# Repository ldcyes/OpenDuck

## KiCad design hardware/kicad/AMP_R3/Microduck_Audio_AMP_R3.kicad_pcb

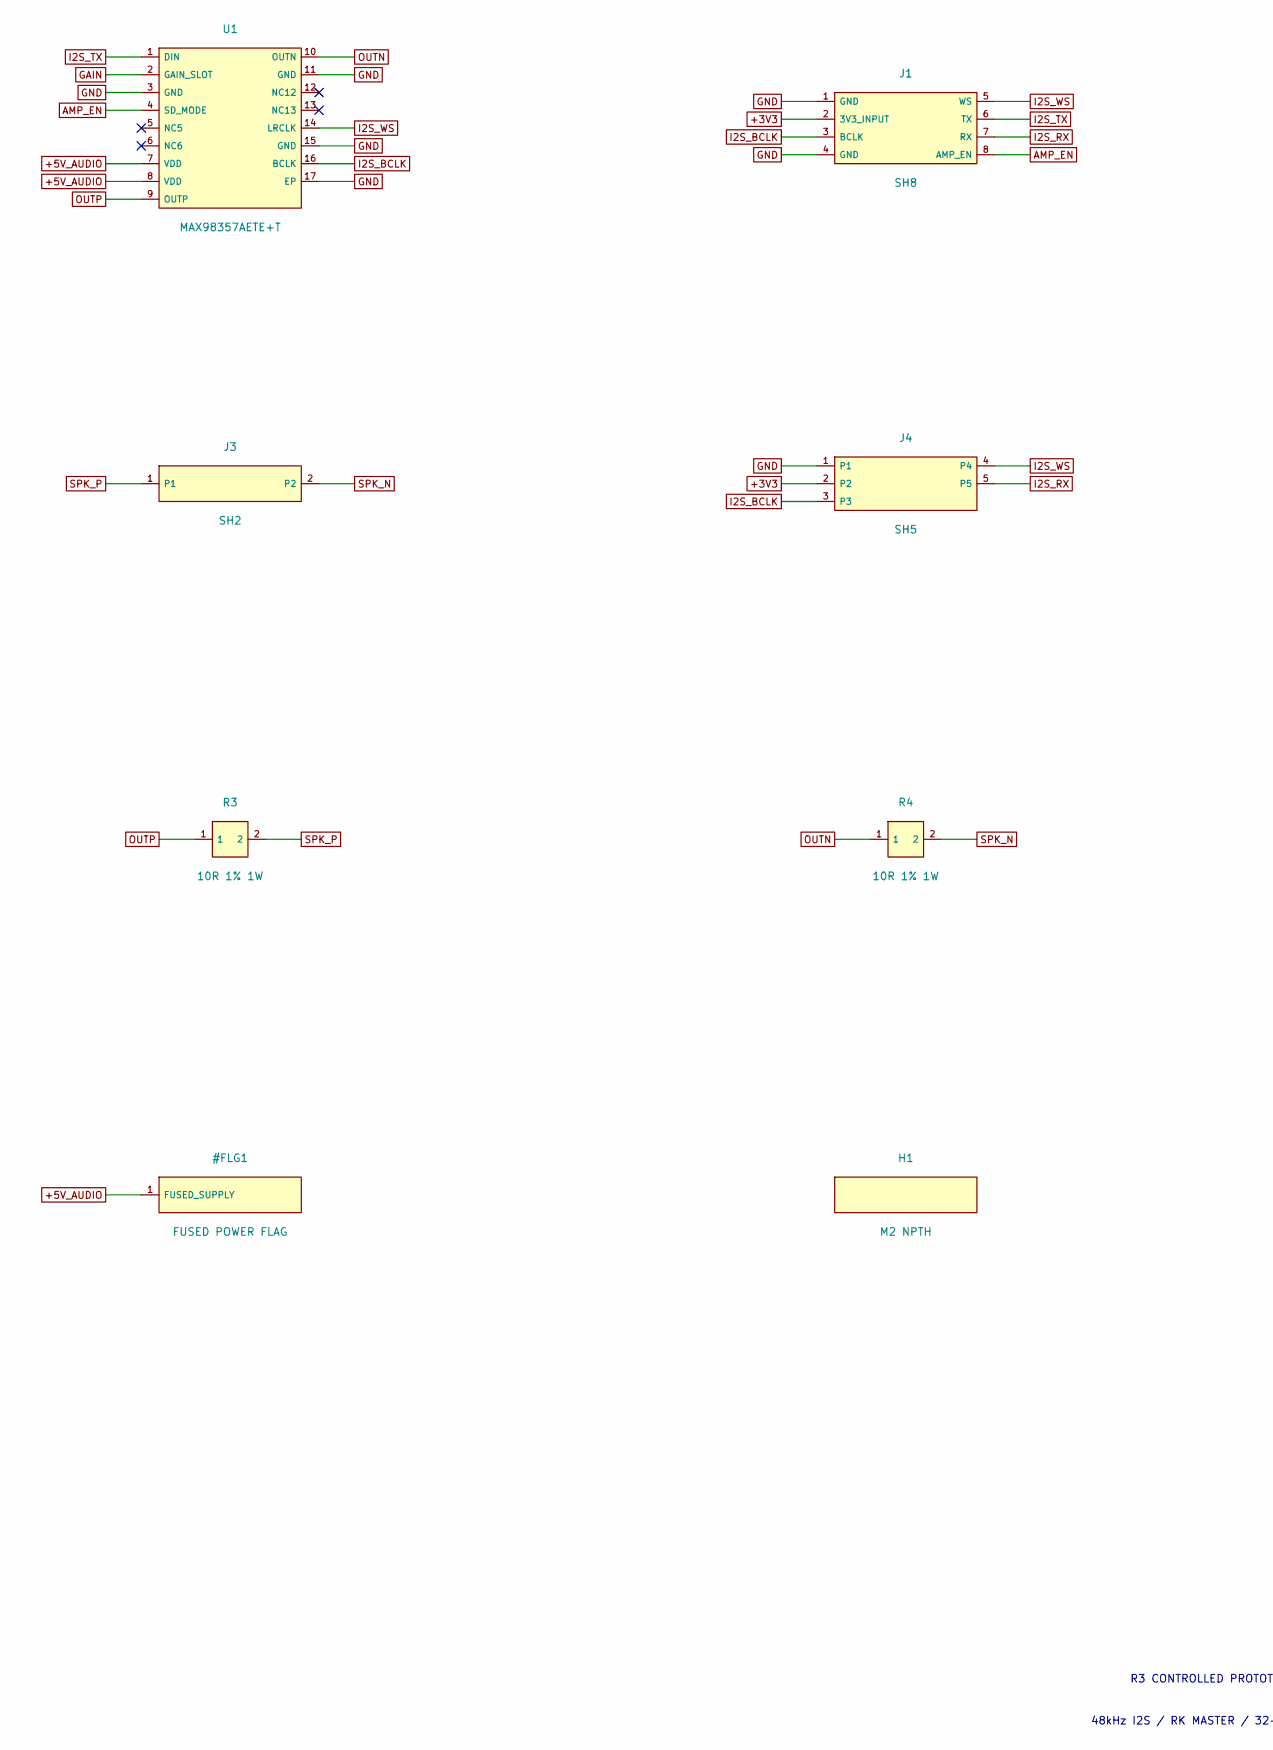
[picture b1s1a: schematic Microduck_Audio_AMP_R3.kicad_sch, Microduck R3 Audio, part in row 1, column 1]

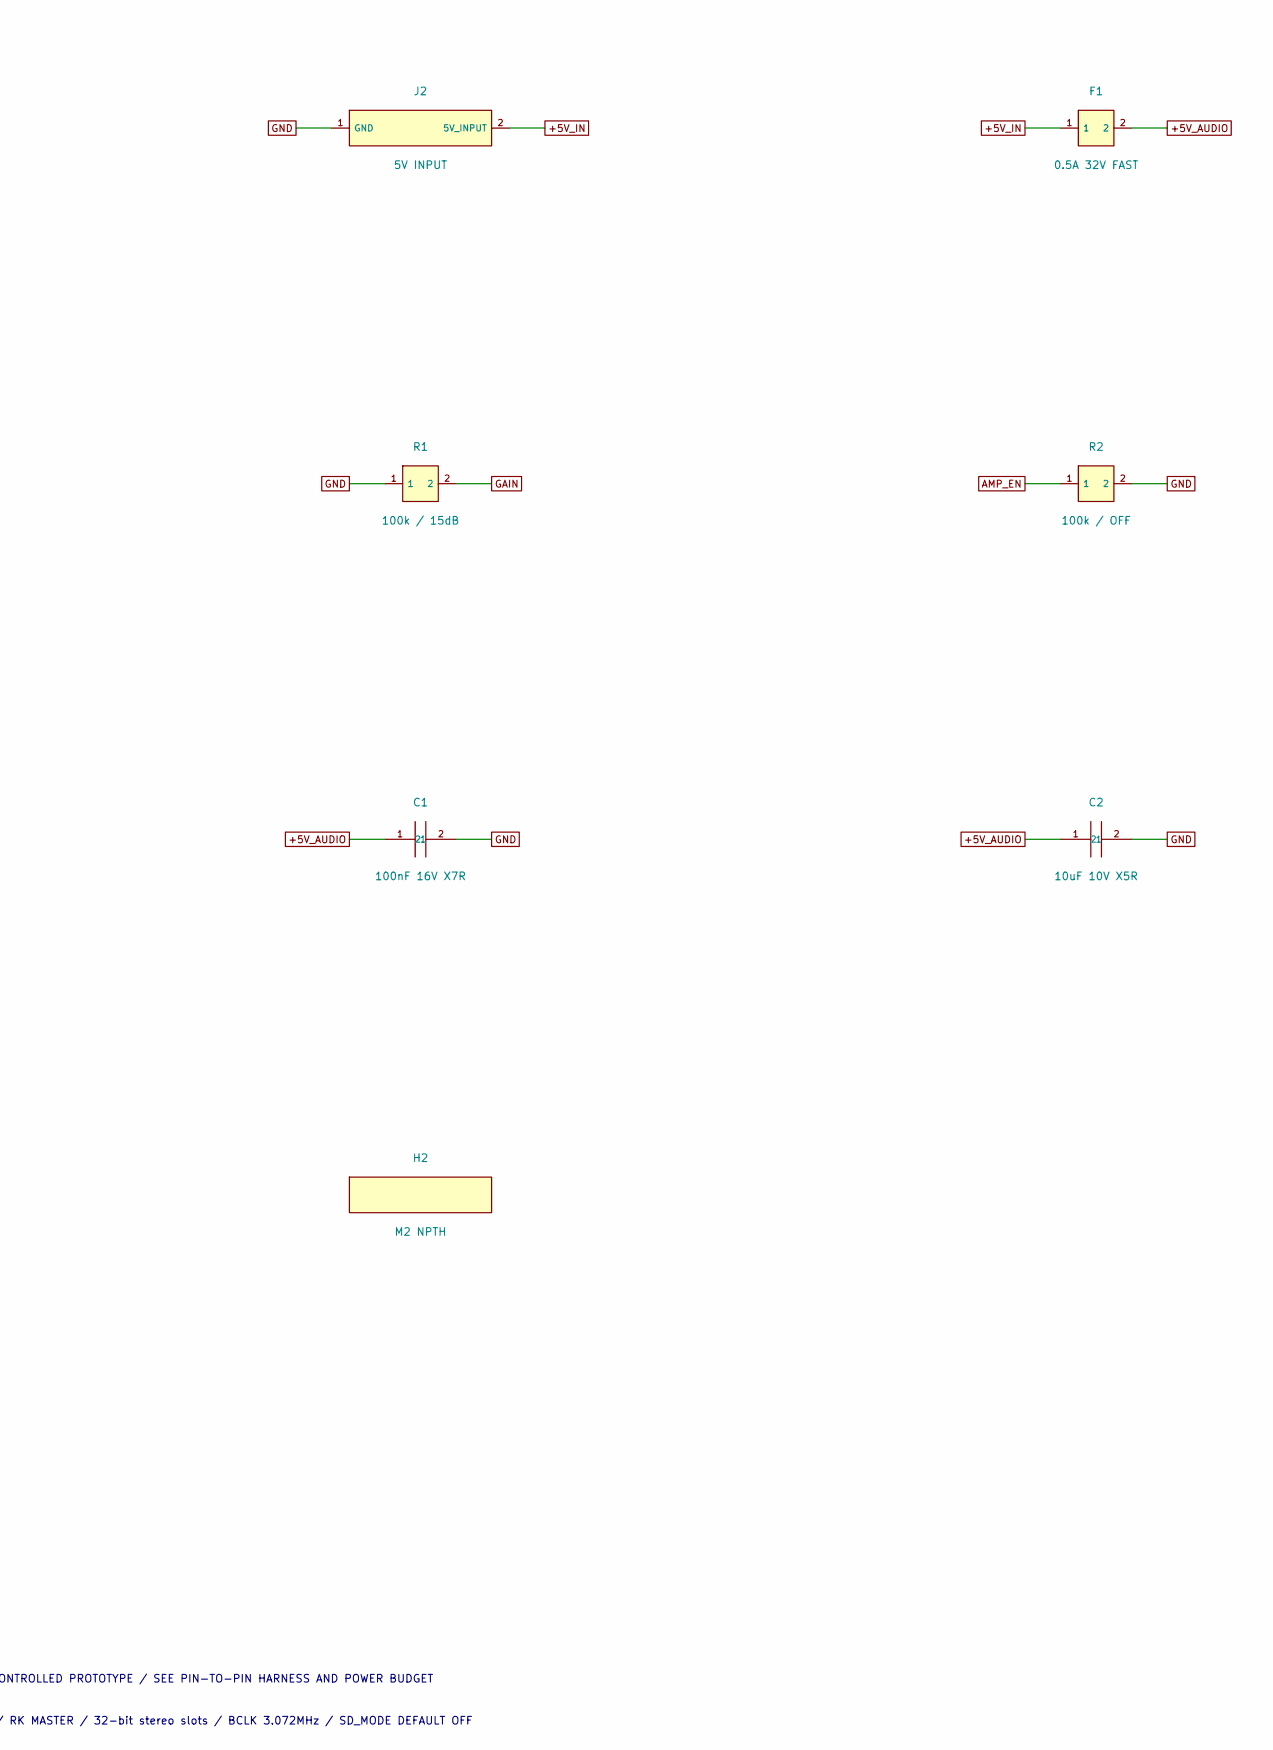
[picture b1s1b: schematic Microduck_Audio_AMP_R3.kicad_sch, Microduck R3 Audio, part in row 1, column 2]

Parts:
C1: 100nF 16V X7R; C_0603_1608Metric; MPN GRM188R71C104KA01D
C2: 10uF 10V X5R; C_0603_1608Metric; MPN GRM188R61A106KE69D
F1: 0.5A 32V FAST; Fuse_0603_1608Metric; MPN 0467.500NR
H1, H2: M2 NPTH; MountingHole_2.2mm_M2; MPN NO PART
J1: SH8; JST_SH_SM08B-SRSS-TB_1x08-1MP_P1.00mm_Horizontal; MPN SM08B-SRSS-TB(LF)(SN)
J2: 5V INPUT; JST_PH_S2B-PH-K_1x02_P2.00mm_Horizontal; MPN S2B-PH-K-S(LF)(SN)
J3: SH2; JST_SH_SM02B-SRSS-TB_1x02-1MP_P1.00mm_Horizontal; MPN SM02B-SRSS-TB(LF)(SN)
J4: SH5; JST_SH_SM05B-SRSS-TB_1x05-1MP_P1.00mm_Horizontal; MPN SM05B-SRSS-TB(LF)(SN)
R1: 100k / 15dB; R_0603_1608Metric; MPN RC0603FR-07100KL
R2: 100k / OFF; R_0603_1608Metric; MPN RC0603FR-07100KL
R3, R4: 10R 1% 1W; R_2512_6332Metric; MPN CRCW251210R0FKEG
U1: MAX98357AETE+T; MAX98357A_T1633_4; MPN MAX98357AETE+T

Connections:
+3V3: J1.2 (3V3_INPUT), J4.2
+5V_AUDIO: C1.1, C2.1, F1.2, U1.7 (VDD), U1.8 (VDD)
+5V_IN: F1.1, J2.2 (5V_INPUT)
AMP_EN: J1.8 (AMP_EN), R2.1, U1.4 (SD_MODE)
GAIN: R1.2, U1.2 (GAIN_SLOT)
GND: C1.2, C2.2, J1.1 (GND), J1.4 (GND), J2.1 (GND), J4.1, R1.1, R2.2, U1.3 (GND), U1.11 (GND), U1.15 (GND), U1.17 (EP)
I2S_BCLK: J1.3 (BCLK), J4.3, U1.16 (BCLK)
I2S_RX: J1.7 (RX), J4.5
I2S_TX: J1.6 (TX), U1.1 (DIN)
I2S_WS: J1.5 (WS), J4.4, U1.14 (LRCLK)
OUTN: R4.1, U1.10 (OUTN)
OUTP: R3.1, U1.9 (OUTP)
SPK_N: J3.2, R4.2
SPK_P: J3.1, R3.2

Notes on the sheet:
R3 CONTROLLED PROTOTYPE / SEE PIN-TO-PIN HARNESS AND POWER BUDGET
48kHz I2S / RK MASTER / 32-bit stereo slots / BCLK 3.072MHz / SD_MODE DEFAULT OFF

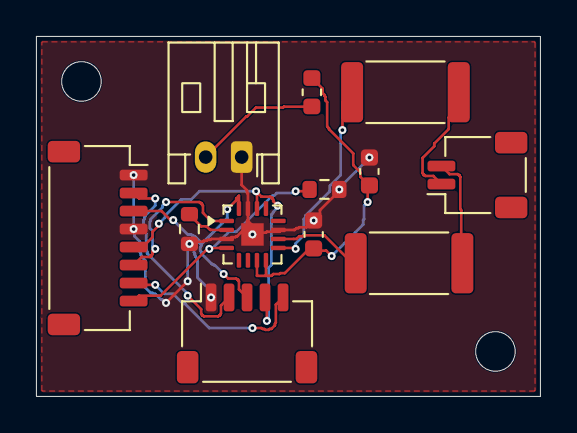
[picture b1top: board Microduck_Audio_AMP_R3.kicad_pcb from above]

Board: 2 copper layers, 28.0 x 20.0 mm, 14 parts (0 on the bottom side), 14 nets.

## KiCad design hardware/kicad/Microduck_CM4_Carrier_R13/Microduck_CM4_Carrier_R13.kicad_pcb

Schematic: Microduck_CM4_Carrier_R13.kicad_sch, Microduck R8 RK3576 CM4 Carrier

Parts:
C1: 4.7nF C0G; C_0603_1608Metric; MPN GRM1885C1H472JA01D
C2, C3: 10uF 10V; C_0805_2012Metric; MPN GRM21BR71A106KE51L
C4: 100nF; C_0603_1608Metric; MPN GRM188R71H104KA93D
F1, F3: .25A; Fuse_0603_1608Metric; MPN 0467.250NRHF
F2: .75A; Fuse_0603_1608Metric; MPN 0467.750NRHF
F4: .5A; Fuse_0603_1608Metric; MPN 0467.500NRHF
H1, H2, H3, H4: M2 NPTH; MountingHole_2.7mm_M2.5; MPN NO PART
J1: SH10; JST_SH_SM10B-SRSS-TB_1x10-1MP_P1.00mm_Horizontal; MPN SM10B-SRSS-TB(LF)(SN)
J2, J4, J5, J6: SH4; JST_SH_SM04B-SRSS-TB_1x04-1MP_P1.00mm_Horizontal; MPN SM04B-SRSS-TB(LF)(SN)
J3: SH8; JST_SH_SM08B-SRSS-TB_1x08-1MP_P1.00mm_Horizontal; MPN SM08B-SRSS-TB(LF)(SN)
J7, J8: SH2; JST_SH_SM02B-SRSS-TB_1x02-1MP_P1.00mm_Horizontal; MPN SM02B-SRSS-TB(LF)(SN)
J101: CM4 J3A 1-100; DF40C_J101; MPN DF40C-100DS-0.4V(51)
J102: CM4 J3B 101-200; DF40C_J102; MPN DF40C-100DS-0.4V(51)
J103: CM4 J1 1-100; DF40C_J103; MPN DF40C-100DS-0.4V(51)
R1: 1.43k 0.1%; R_0603_1608Metric; MPN RT0603BRD071K43L
R2, R3: 100k; R_0603_1608Metric; MPN ERJ-3EKF1003V
R4, R5, R6: 22R; R_0603_1608Metric; MPN ERJ-3EKF22R0V
R7: 10k 1%; R_0603_1608Metric; MPN ERJ-3EKF1002V
R8: 20k 1%; R_0603_1608Metric; MPN ERJ-3EKF2002V
TP1: VBUSDET_TP; Test_SMD1; MPN TEST ONLY
TP2: OTG_VBUS_ONLY; Test_SMD1; MPN TEST ONLY
TP3: MASKROM; Test_SMD1; MPN TEST ONLY
TP4: RESET_N; Test_SMD1; MPN TEST ONLY
TP5: PWRON_N; Test_SMD1; MPN TEST ONLY
TP6: GND; Test_SMD1; MPN TEST ONLY
TP7: CORE_FAULT_N; Test_SMD1; MPN TEST ONLY
TP8: TDK_IMON; Test_SMD1; MPN TEST ONLY
TP9: BRAKE_ACTIVE_N; Test_SMD1; MPN TEST ONLY
U1: CORE 1.439A EFUSE; Texas_DSG0008A_WSON-8-1EP_2x2mm_P0.5mm_EP0.9x1.6mm; MPN TPS259530DSGR
U2, U3, U4: USB2 ESD; SOT-23-6; MPN USBLC6-2SC6
W1: SYSTEM_5V IN; Wire_SMD4; MPN SOLDER AWG20
W2: SYSTEM GND; Wire_SMD4; MPN SOLDER AWG20

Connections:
+3V3: J1.2, J2.2, J3.2, J101.78 (GPIO_VREF), J101.84 (VCCIO6), J101.86 (VCCIO6)
AMP_ENABLE: J3.8, J101.37 (SPI1_CSN1_M0), R3.1
AUDIO_5V: F4.2, J8.2
BRAKE_ACTIVE_N: J1.8, TP9.1
CORE_5V: C3.1, C4.1, J101.77 (5V_DCIN), J101.79 (5V_DCIN), J101.81 (5V_DCIN), J101.83 (5V_DCIN), J101.85 (5V_DCIN), J101.87 (5V_DCIN), U1.5 (OUT)
CORE_DVDT: C1.1, U1.1 (dVdt)
CORE_FAULT_N: TP7.1, U1.6 (FAULT_N)
CORE_ILM: R1.1, U1.7 (ILM)
FAN_5V: F3.2, J7.2
GND: C1.2, C2.2, C3.2, C4.2, J1.1, J1.9, J1.10, J2.1, J3.1, J3.4, J4.4, J5.4, J6.4, J7.1, J8.1, J101.1 (GND), J101.2 (GND), J101.7 (GND), J101.8 (GND), J101.13 (GND), J101.14 (GND), J101.22 (GND), J101.23 (GND), J101.32 (GND), J101.33 (GND), J101.42 (GND), J101.43 (GND), J101.52 (GND), J101.53 (GND), J101.59 (GND), J101.60 (GND), J101.65 (GND), J101.66 (GND), J101.71 (GND), J101.74 (GND), J101.98 (GND), J102.7 (GND), J102.8 (GND), J102.13 (GND), J102.14 (GND), J102.19 (GND), J102.20 (GND), J102.25 (GND), J102.26 (GND), J102.31 (GND), J102.32 (GND), J102.37 (GND), J102.38 (GND), J102.44 (GND), J102.50 (GND), J102.55 (GND), J102.56 (GND), J102.61 (GND), J102.62 (GND), J102.67 (GND), J102.68 (GND), J102.73 (GND), J102.74 (GND), J102.79 (GND), J102.80 (GND), J102.85 (GND), J102.86 (GND), J102.91 (GND), J102.92 (GND), J102.97 (GND), J102.98 (GND), J103.1 (GND), J103.2 (GND), J103.8 (GND), J103.14 (GND), J103.20 (GND), J103.21 (GND), J103.26 (GND), J103.31 (GND), J103.32 (GND), J103.38 (GND), J103.41 (GND), J103.44 (GND), J103.47 (GND), J103.50 (GND), J103.55 (GND), J103.56 (GND), J103.61 (GND), J103.62 (GND), J103.67 (GND), J103.68 (GND), J103.71 (GND), J103.74 (GND), J103.75 (GND), J103.99 (GND), J103.100 (GND), R1.2, R2.2, R3.2, R8.2, TP6.1, U1.8 (GND), U1.9 (EP), U2.2 (GND), U3.2 (GND), U4.2 (GND), W2.1
I2C_SCL: J1.4, J2.4, J101.56 (I2C8_SCL_M1)
I2C_SDA: J1.3, J2.3, J101.58 (I2C8_SDA_M1)
I2S_BCLK: J3.3, R4.2
I2S_BCLK_CORE: J103.25 (SAI1_SCLK_M0), R4.1
I2S_RX: J3.7, J103.27 (SAI1_SDI0_M0)
I2S_TX: J3.6, R6.2
I2S_TX_CORE: J103.29 (SAI1_SDO0_M0), R6.1
I2S_WS: J3.5, R5.2
I2S_WS_CORE: J103.19 (SAI1_LRCK_M0), R5.1
MASKROM: J101.93 (MASKROM), TP3.1
OTG_DM: J6.2, J102.3 (USB2_OTG0_DM), U4.1 (IO), U4.6 (IO)
OTG_DP: J6.3, J102.5 (USB2_OTG0_DP), U4.3 (IO), U4.4 (IO)
OTG_VBUS_ONLY: J6.1, R7.1, TP2.1, U4.5 (VBUS)
PWRON_N: J101.99 (PWRON_L), TP5.1
RESET_N: J101.92 (RESET_L), TP4.1
RUN_OK: J1.6, J101.28 (SPI2_MOSI_M1)
RUN_REQ: J1.5, J101.30 (GPIO1_C1), R2.1
SYSTEM_5V: C2.1, F1.1, F2.1, F3.1, F4.1, U1.2 (EN), U1.3 (IN), U1.4 (IN), W1.1
TDK_IMON: J1.7, TP8.1
U2D2_5V: F1.2, J4.1, U2.5 (VBUS)
U2D2_DM: J4.2, J103.66 (USB20_2DM), U2.1 (IO), U2.6 (IO)
U2D2_DP: J4.3, J103.64 (USB20_2DP), U2.3 (IO), U2.4 (IO)
UVC_5V: F2.2, J5.1, U3.5 (VBUS)
UVC_DM: J5.2, J103.72 (USB20_3DM), U3.1 (IO), U3.6 (IO)
UVC_DP: J5.3, J103.70 (USB20_3DP), U3.3 (IO), U3.4 (IO)
VBUSDET_TP: J103.98 (USB2_OTG0_VBUSDET), R7.2, R8.1, TP1.1

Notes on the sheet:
RK3576 CM4 V1.20 / 5V protected carrier / Mated height1.5mm / 300 official contacts
J101/J102 map CM4 J3A/J3B; J103 maps CM4 J1. NO inherited ZERO3W or Q38 pin mapping.
VBUSDET uses official10k/20k divider plus internal40k; C1404 already on CM4. Never connect USB VBUS directly to core detect or5V rail.

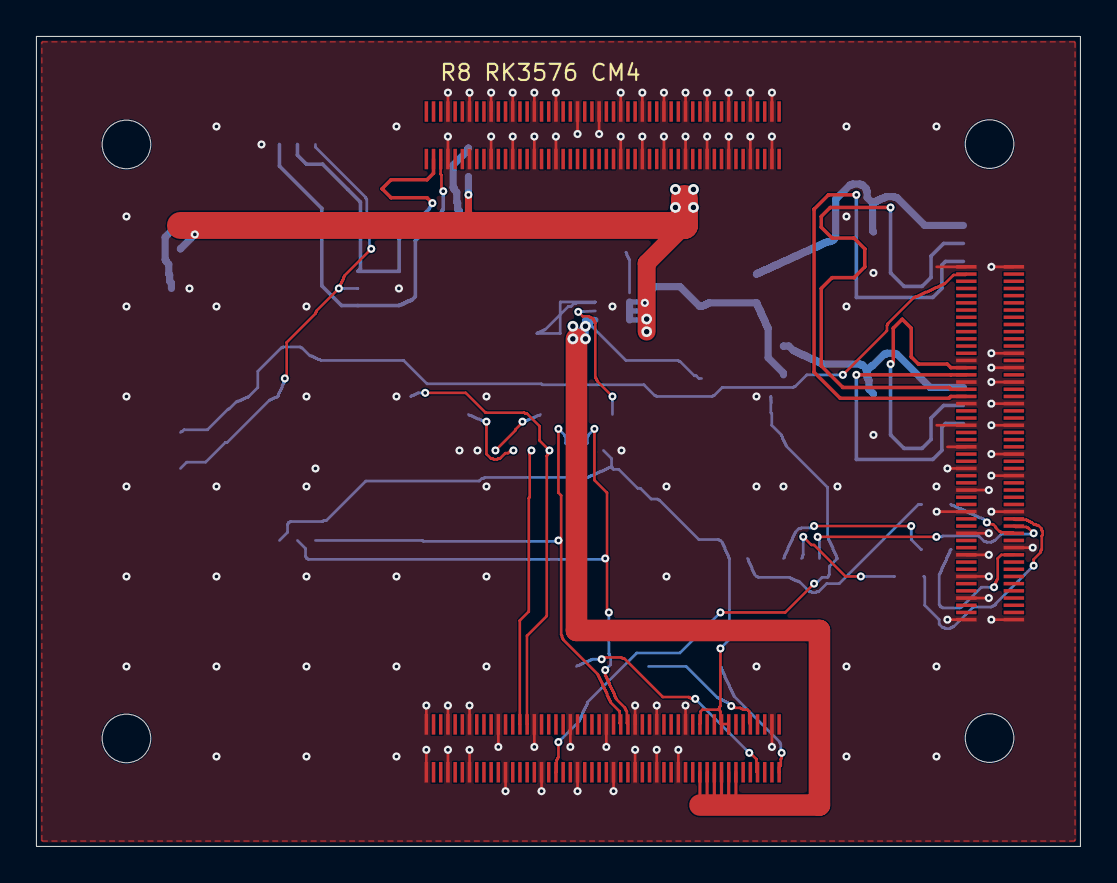
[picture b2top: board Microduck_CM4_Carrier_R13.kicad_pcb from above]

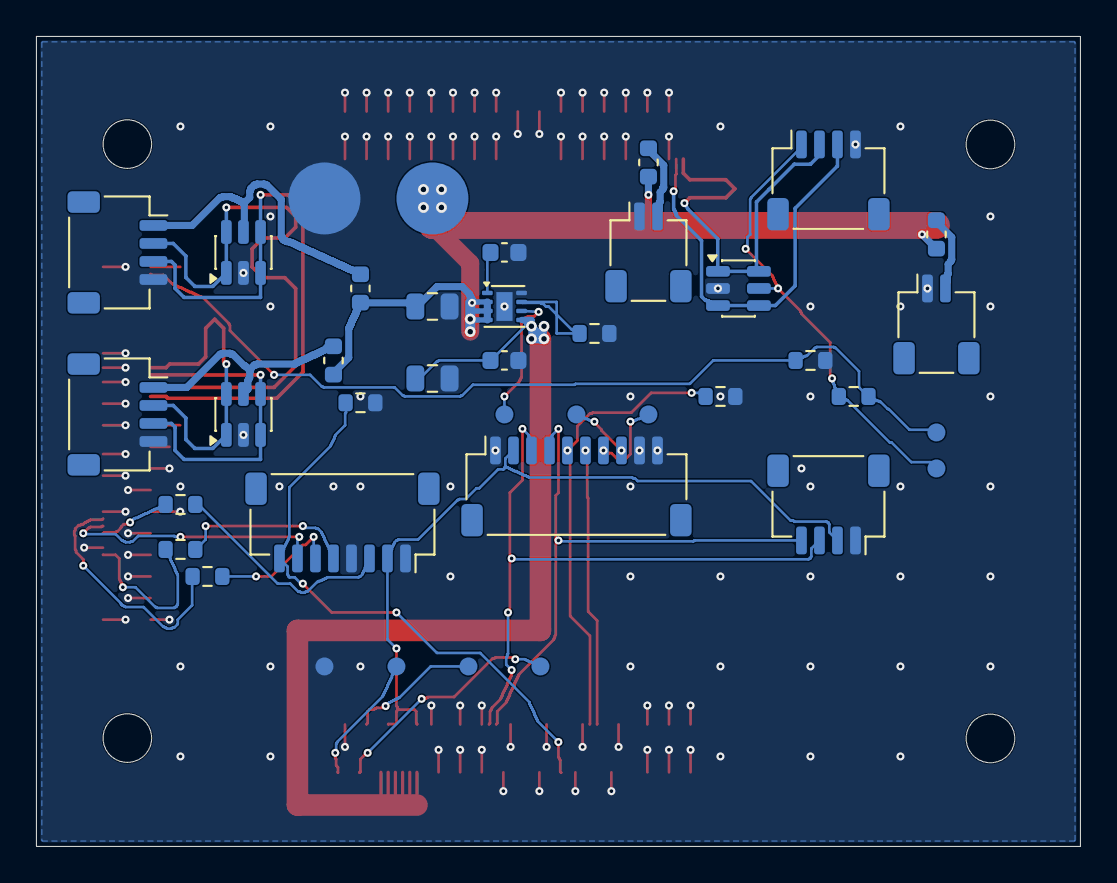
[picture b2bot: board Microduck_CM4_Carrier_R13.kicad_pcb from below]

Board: 4 copper layers, 58.0 x 45.0 mm, 46 parts (39 on the bottom side), 36 nets.

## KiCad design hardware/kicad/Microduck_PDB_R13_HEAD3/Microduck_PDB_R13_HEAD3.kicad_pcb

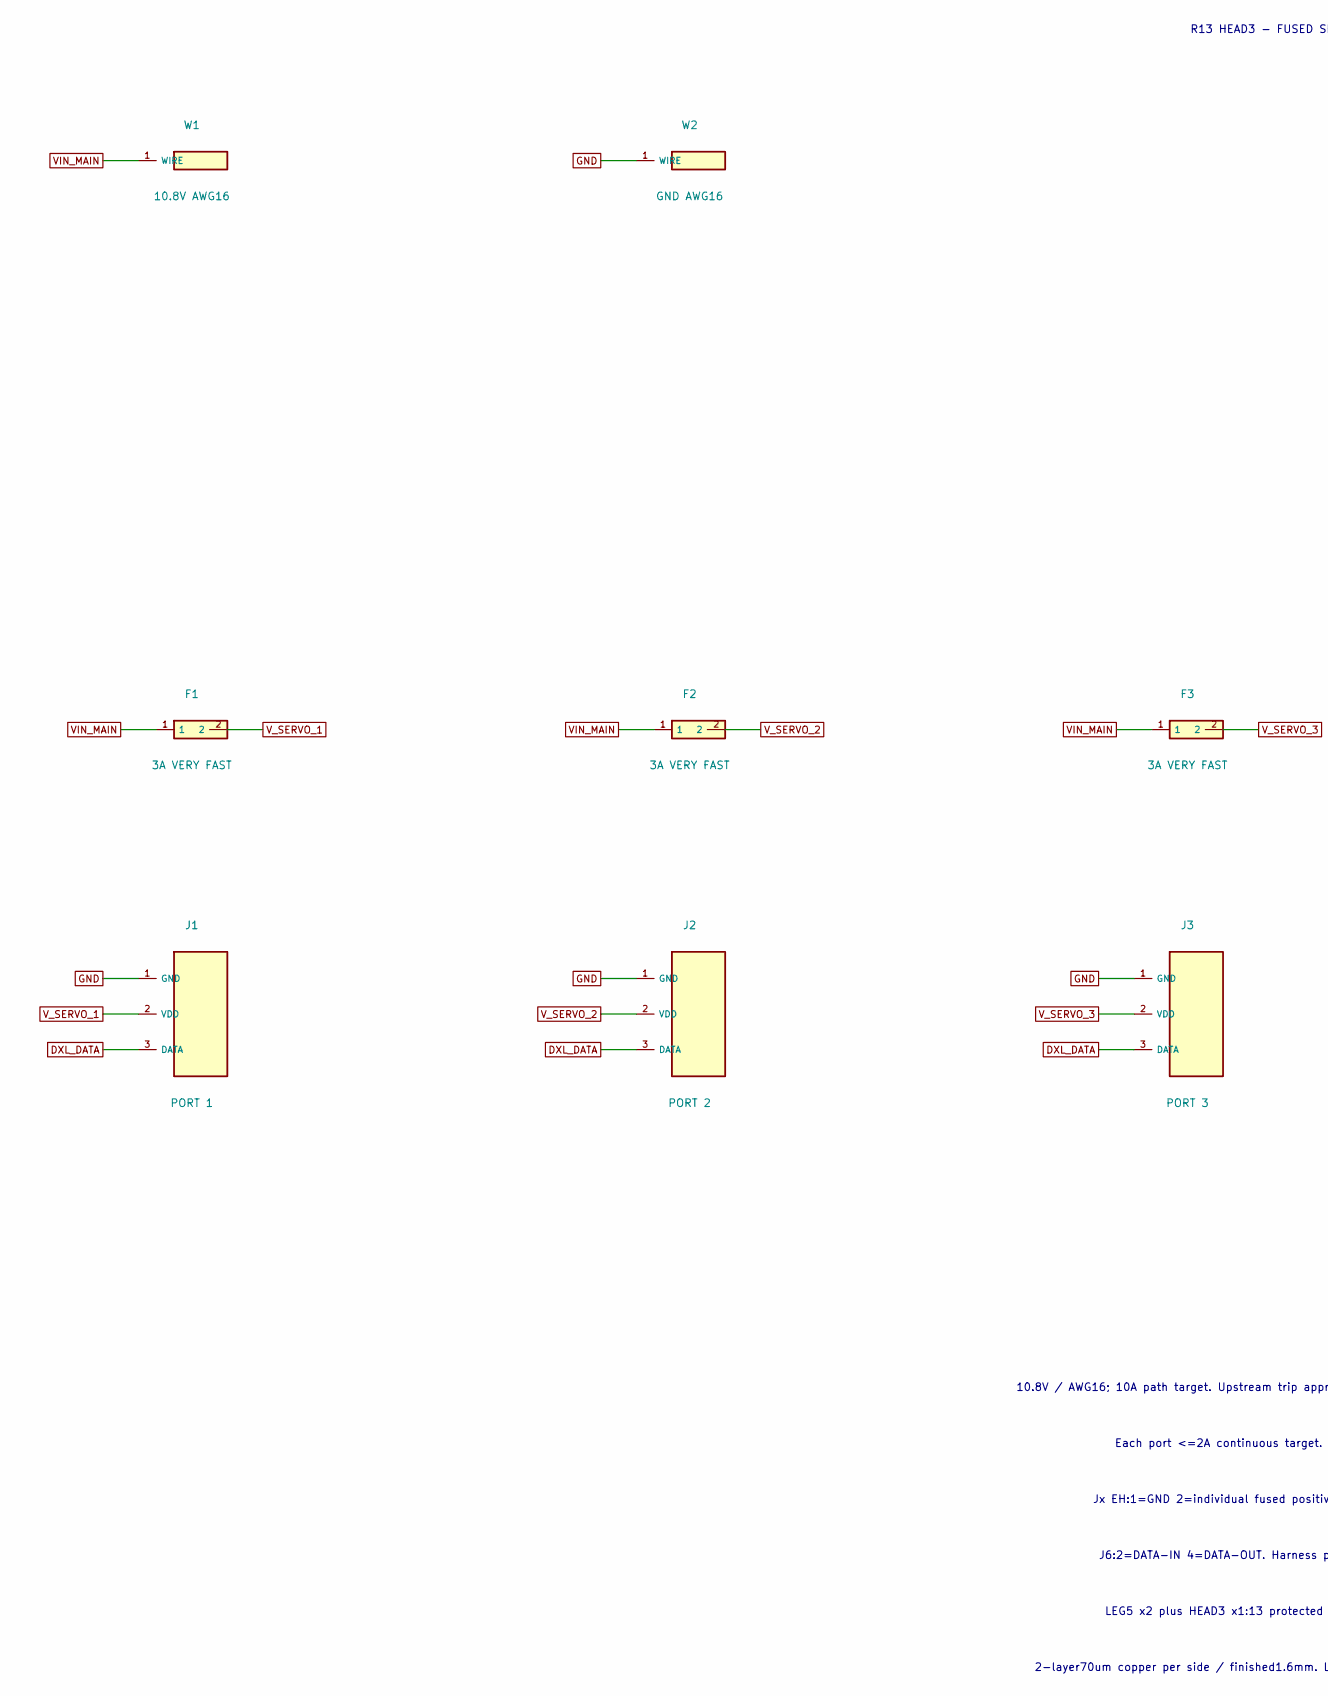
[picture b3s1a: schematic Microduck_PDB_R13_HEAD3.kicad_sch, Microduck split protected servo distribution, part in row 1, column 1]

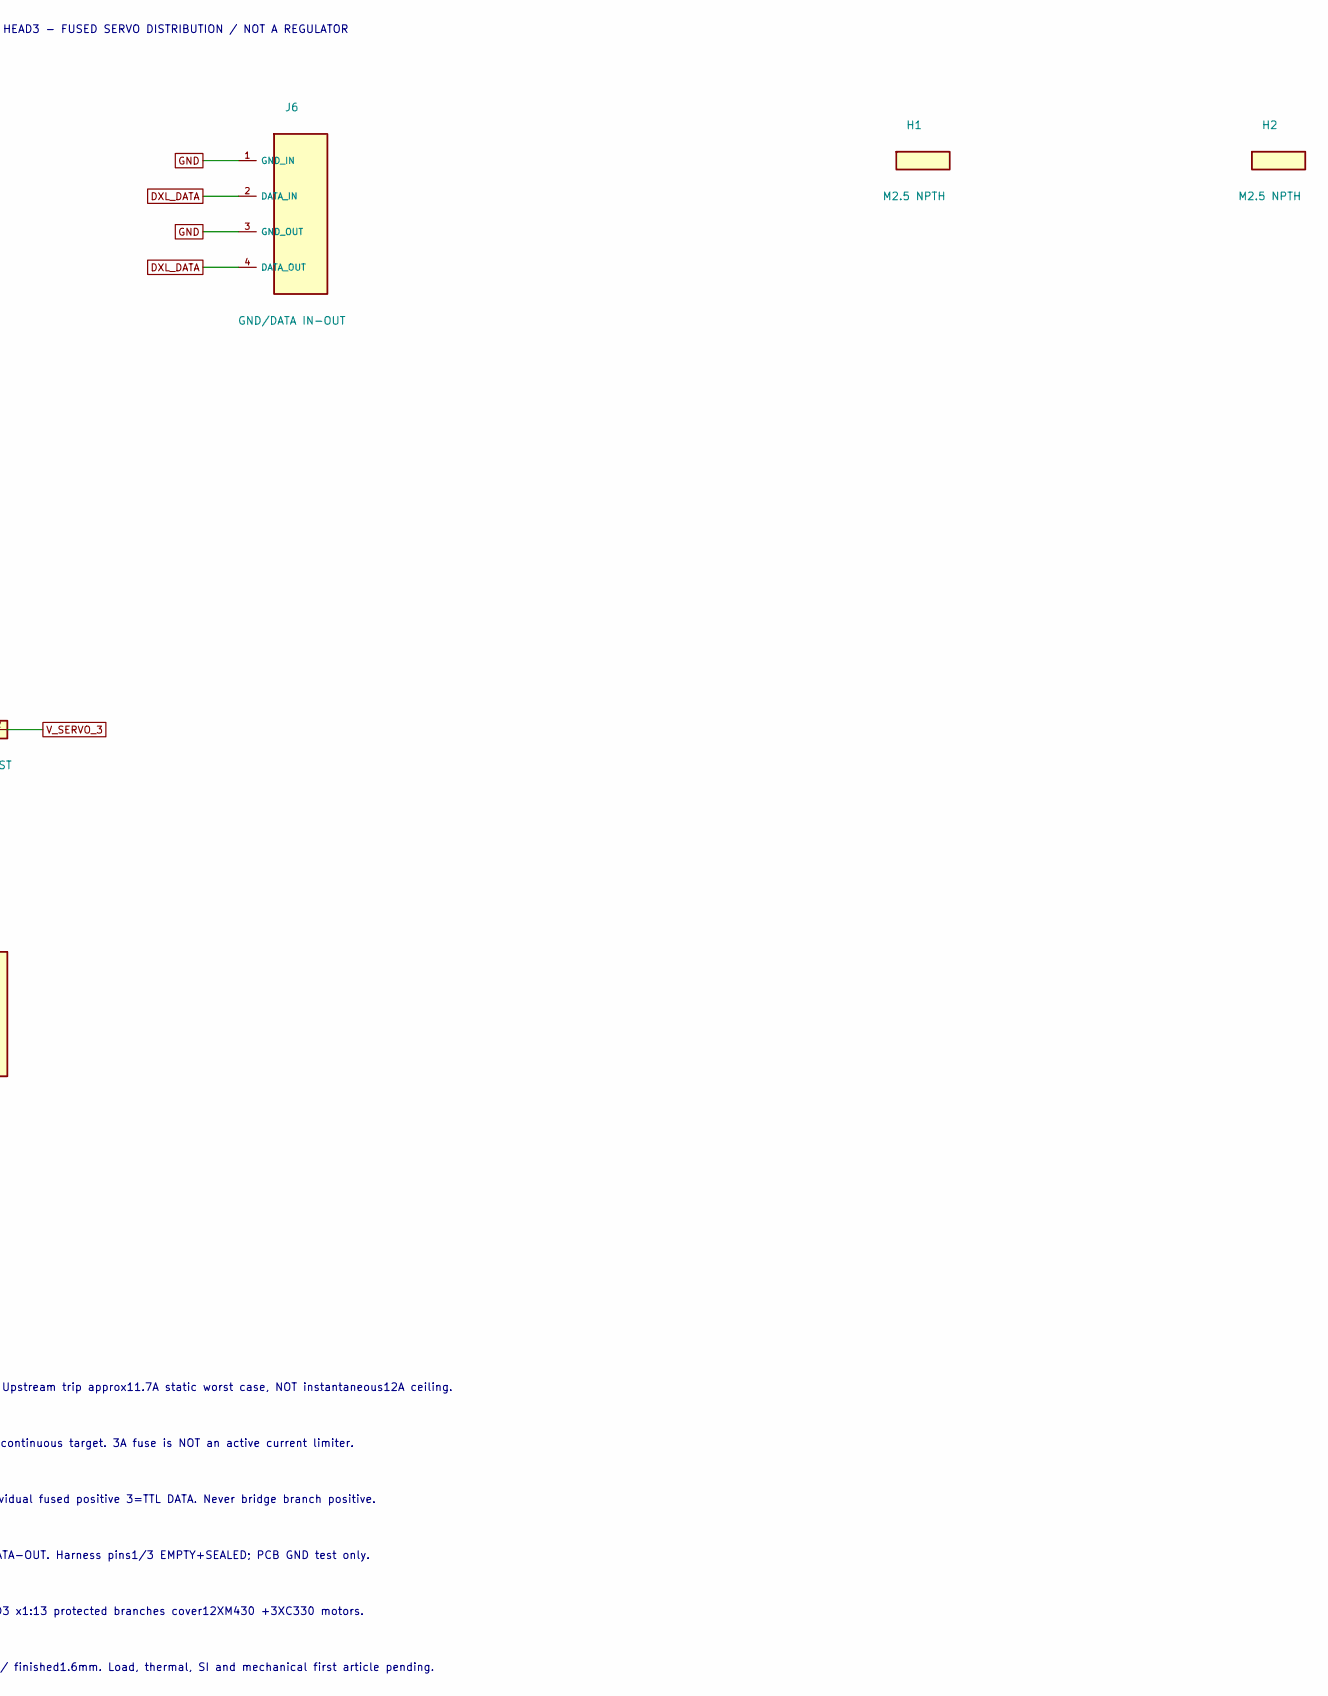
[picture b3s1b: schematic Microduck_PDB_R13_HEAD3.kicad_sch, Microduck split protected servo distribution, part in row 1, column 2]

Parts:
F1, F2, F3: 3A VERY FAST; Fuse_Littelfuse_448; MPN 0448003.MR
H1, H2: M2.5 NPTH; MountingHole_2.7mm_M2.5; MPN NO PART
J1: PORT 1; JST_EH_S3B-EH_1x03_P2.50mm_Horizontal; MPN S3B-EH(LF)(SN)
J2: PORT 2; JST_EH_S3B-EH_1x03_P2.50mm_Horizontal; MPN S3B-EH(LF)(SN)
J3: PORT 3; JST_EH_S3B-EH_1x03_P2.50mm_Horizontal; MPN S3B-EH(LF)(SN)
J6: GND/DATA IN-OUT; JST_SH_SM04B-SRSS-TB_1x04-1MP_P1.00mm_Horizontal; MPN SM04B-SRSS-TB(LF)(SN)
W1: 10.8V AWG16; WirePad_2p4mm_6mm; MPN WIRE55A0111-16-2
W2: GND AWG16; WirePad_2p4mm_6mm; MPN WIRE55A0111-16-0

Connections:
DXL_DATA: J1.3 (DATA), J2.3 (DATA), J3.3 (DATA), J6.2 (DATA_IN), J6.4 (DATA_OUT)
GND: J1.1 (GND), J2.1 (GND), J3.1 (GND), J6.1 (GND_IN), J6.3 (GND_OUT), W2.1
VIN_MAIN: F1.1, F2.1, F3.1, W1.1
V_SERVO_1: F1.2, J1.2 (VDD)
V_SERVO_2: F2.2, J2.2 (VDD)
V_SERVO_3: F3.2, J3.2 (VDD)

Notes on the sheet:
R13 HEAD3 - FUSED SERVO DISTRIBUTION / NOT A REGULATOR
10.8V / AWG16; 10A path target. Upstream trip approx11.7A static worst case, NOT instantaneous12A ceiling.
Each port <=2A continuous target. 3A fuse is NOT an active current limiter.
Jx EH:1=GND 2=individual fused positive 3=TTL DATA. Never bridge branch positive.
J6:2=DATA-IN 4=DATA-OUT. Harness pins1/3 EMPTY+SEALED; PCB GND test only.
LEG5 x2 plus HEAD3 x1:13 protected branches cover12XM430 +3XC330 motors.
2-layer70um copper per side / finished1.6mm. Load, thermal, SI and mechanical first article pending.

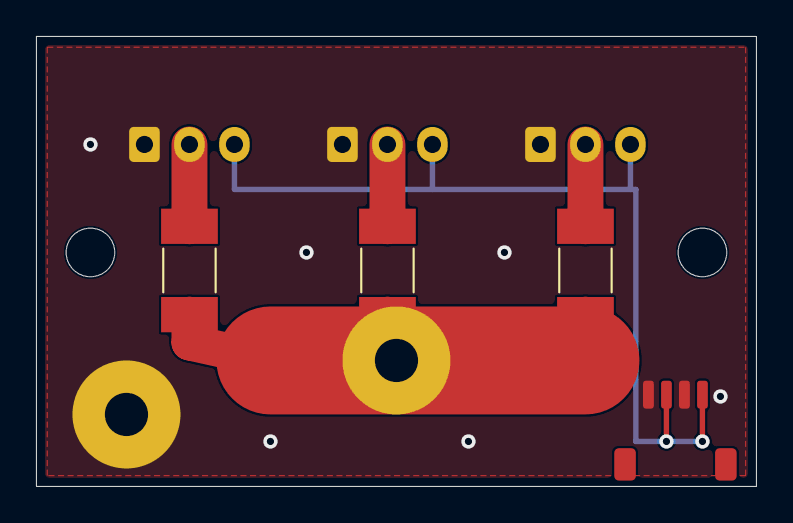
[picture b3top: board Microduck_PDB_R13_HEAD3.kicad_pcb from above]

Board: 2 copper layers, 40.0 x 25.0 mm, 11 parts (0 on the bottom side), 6 nets.

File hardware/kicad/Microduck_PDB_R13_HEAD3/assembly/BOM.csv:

Reference,Quantity,MPN,Value,Footprint,Mounting,Scope,Datasheet
J1,1,S3B-EH(LF)(SN),PORT 1,Connector_JST:JST_EH_S3B-EH_1x03_P2.50mm_Horizontal,THT,one PCB; matching housings/terminals in harness BOM,https://www.jst-mfg.com/product/pdf/eng/eEH.pdf
F1,1,0448003.MR,3A VERY FAST,Microduck_PDB_R13:Fuse_Littelfuse_448,SMT,one PCB; matching housings/terminals in harness BOM,https://www.littelfuse.com/assetdocs/littelfuse_fuse_448_dat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
J2,1,S3B-EH(LF)(SN),PORT 2,Connector_JST:JST_EH_S3B-EH_1x03_P2.50mm_Horizontal,THT,one PCB; matching housings/terminals in harness BOM,https://www.jst-mfg.com/product/pdf/eng/eEH.pdf
F2,1,0448003.MR,3A VERY FAST,Microduck_PDB_R13:Fuse_Littelfuse_448,SMT,one PCB; matching housings/terminals in harness BOM,https://www.littelfuse.com/assetdocs/littelfuse_fuse_448_dat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
J3,1,S3B-EH(LF)(SN),PORT 3,Connector_JST:JST_EH_S3B-EH_1x03_P2.50mm_Horizontal,THT,one PCB; matching housings/terminals in harness BOM,https://www.jst-mfg.com/product/pdf/eng/eEH.pdf
F3,1,0448003.MR,3A VERY FAST,Microduck_PDB_R13:Fuse_Littelfuse_448,SMT,one PCB; matching housings/terminals in harness BOM,https://www.littelfuse.com/assetdocs/littelfuse_fuse_448_dat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
J6,1,SM04B-SRSS-TB(LF)(SN),GND/DATA IN-OUT,Connector_JST:JST_SH_SM04B-SRSS-TB_1x04-1MP_P1.00mm_Horizontal,SMT,one PCB; matching housings/terminals in harness BOM,https://www.jst-mfg.com/product/pdf/eng/eSH.pdf
